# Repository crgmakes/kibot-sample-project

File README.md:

# Kibot Sample
All the source files for the Kibot Sample project

# Software 

You will need [KiCad](https://kicad.org) to view and edit this design. Click [here](https://www.kicad.org/download/) to download.

---

THE DESIGN IS PROVIDED "AS IS" AND THE AUTHOR DISCLAIMS ALL WARRANTIES WITH REGARD TO THIS DESIGN INCLUDING ALL IMPLIED WARRANTIES OF MERCHANTABILITY AND FITNESS. IN NO EVENT SHALL THE AUTHOR BE LIABLE FOR ANY SPECIAL, DIRECT, INDIRECT, OR CONSEQUENTIAL DAMAGES OR ANY DAMAGES WHATSOEVER RESULTING FROM LOSS OF USE, DATA OR PROFITS, WHETHER IN AN ACTION OF CONTRACT, NEGLIGENCE OR OTHER TORTIOUS ACTION, ARISING OUT OF OR IN CONNECTION WITH THE USE OR PERFORMANCE OF THIS DESIGN.

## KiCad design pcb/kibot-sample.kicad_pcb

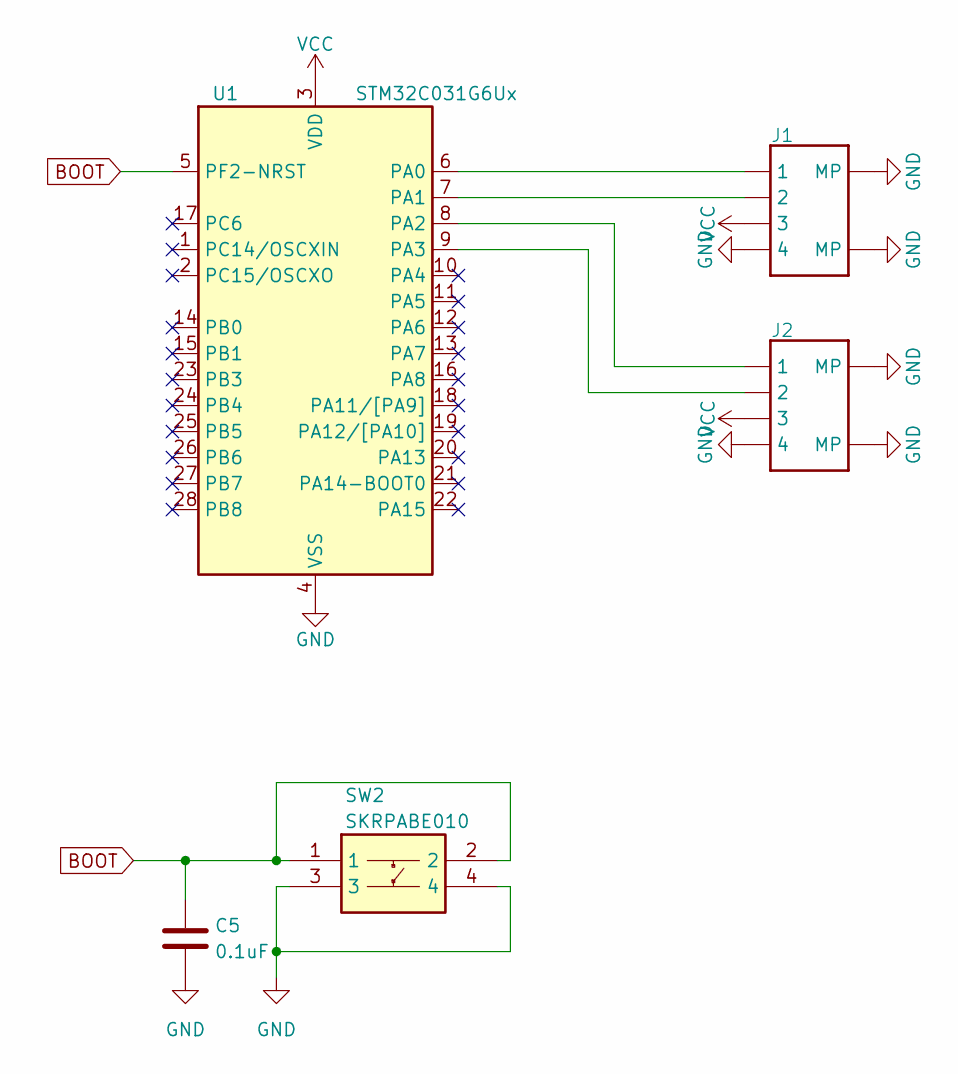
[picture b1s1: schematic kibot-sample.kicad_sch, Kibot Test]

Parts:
C5: 0.1uF; C_0603_1608Metric; Tolerance 10%; MPN CL10B104KO8NNNC; Digikey 1276-1005-2-ND
J1, J2: JST_SH_BM04B-SRSS-TB_1x04-1MP_P1.00mm_Vertical; MPN BM04B-SRSS-TBT(LF)(SN); Mouser 306-BM04BSRSSTBTLFSN
SW2: SKRPABE010; SMD-4P-4.2x3.2mm; MPN SKRPABE010; Digikey 4809-SKRPABE010TR-ND
U1: STM32C031G6Ux; QFN-28_4x4mm_P0.5mm; Digikey 497-STM32C031G6U6-ND

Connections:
BOOT: C5.1, SW2.1, SW2.2, U1.5 (PF2-NRST)
GND: C5.2, J1.0 (MP), J1.4, J1.5 (MP), J2.0 (MP), J2.4, J2.5 (MP), SW2.3, SW2.4, U1.4 (VSS)
unnamed: J1.1, U1.6 (PA0)
unnamed: J1.2, U1.7 (PA1)
unnamed: J2.1, U1.8 (PA2)
unnamed: J2.2, U1.9 (PA3)
VCC: J1.3, J2.3, U1.3 (VDD)

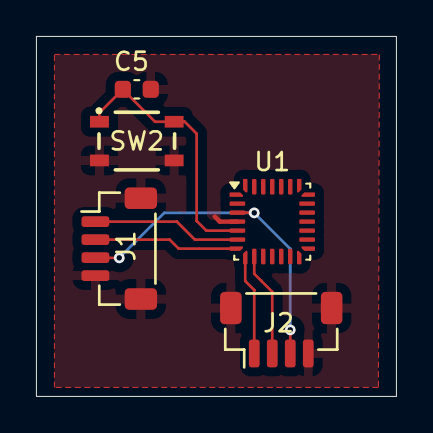
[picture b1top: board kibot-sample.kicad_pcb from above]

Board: 4 copper layers, 20.0 x 20.0 mm, 5 parts (0 on the bottom side), 7 nets.

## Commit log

2026-06-17 Initial check in
2026-06-17 fixed board layers
2026-06-17 fixed script call
2026-06-23 Moved files to be local and simplified
2026-06-23 fixed file path
2026-06-23 fixed path to kibot
2026-06-23 fixed path to ecad
2026-06-23 fixed version on ecad
2026-06-24 moved everything to single script
2026-06-24 fixed jobs header
2026-06-24 try again
2026-06-24 updated use statement
2026-06-24 moved inputs to env variables
2026-06-24 commented out everything in ecad
2026-06-24 call latest and previous
2026-06-24 fixed version on include
2026-06-24 fixed names and locations
2026-06-24 fixed input variables
